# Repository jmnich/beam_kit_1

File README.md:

# Beam Kit 1

Open Source educational eval kit built around Raspberry Pi Pico. Designed for Raspberry Pi Pico 2W.

## 🚀 Features
- Socket for RPI Pico module
- Integrated debug probe with separate USB C socket, allowing for powering, programming and debugging the kit with a single cable
- I2C sensors, EEPROM and laser range finder
- Micro SD slot
- 4x4 WS2812 LED matrix
- industrial RS485 interface
- basic audio: analog microphone and stereo minijack output
- HAT socket
- SSD1306 OLED display
- NRF24 socket
- LEDs, knob and buttons

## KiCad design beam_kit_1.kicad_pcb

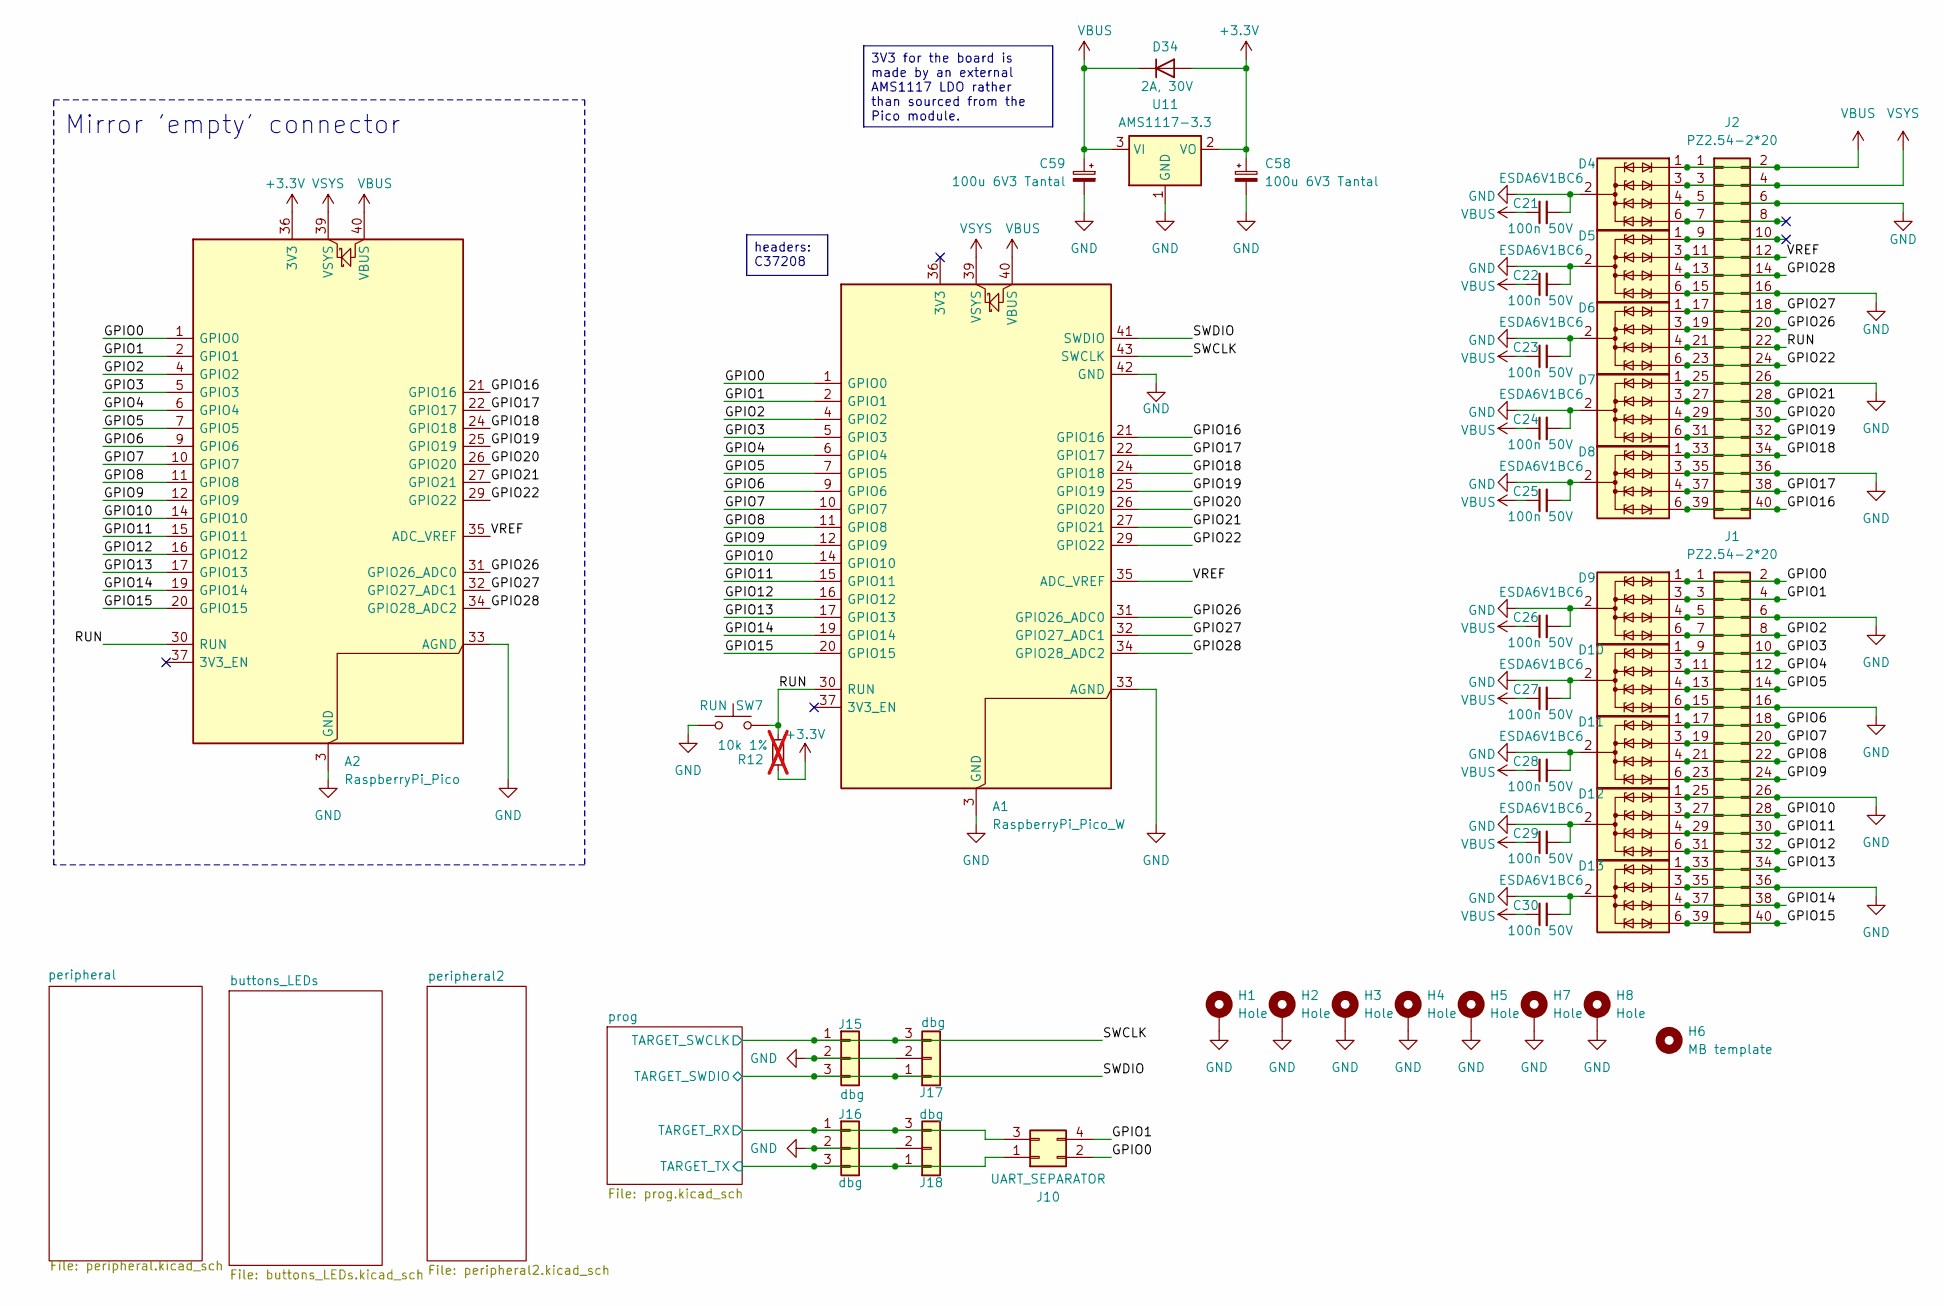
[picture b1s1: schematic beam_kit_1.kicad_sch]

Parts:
A1: RaspberryPi_Pico_W; RaspberryPi_Pico_Common
A2: RaspberryPi_Pico; RaspberryPi_Pico_Common
C21, C22, C23, C24, C25, C26, C27, C28, C29, C30: 100n 50V; C_0603_1608Metric_Pad1.08x0.95mm_HandSolder; jlc C14663
C58, C59: 100u 6V3 Tantal; CP_EIA-3528-21_Kemet-B_Pad1.50x2.35mm_HandSolder; jlc C16133
D4, D5, D6, D7, D8, D9, D10, D11, D12, D13: ESDA6V1BC6; SOT-23-6; MPN ESDA6V1BC6; jlc C495220
D34: 2A, 30V; D_PowerDI-123; MPN DFLS230LH-7; jlc C2960361
H1, H2, H3, H4, H5, H7, H8: Hole; MountingHole_3.2mm_M3_Pad_Via
H6: MB template; MountingHole_2.1mm
J1, J2: PZ2.54-2*20; PinHeader_2x20_P2.54mm_Vertical; jlc C5224014
J10: UART_SEPARATOR; PinHeader_2x02_P2.54mm_Vertical; jlc C7501273
J15, J16, J17, J18: dbg; JST_SH_BM03B-SRSS-TB_1x03-1MP_P1.00mm_Vertical; jlc C495538
R12: 10k 1%; R_0603_1608Metric_Pad0.98x0.95mm_HandSolder; jlc C25804; not fitted
SW7: RUN; SW_Push_1P1T_NO_6x6mm_H9.5mm; jlc C455112
U11: AMS1117-3.3; SOT-223-3_TabPin2; jlc C6186

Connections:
+3.3V: A2.36 (3V3), C58.1, D34.2 (A), R12.2, U11.2 (VO); also elsewhere on the board
/GPIO0: A1.1 (GPIO0), A2.1 (GPIO0), D9.1 (TVS1), J1.1, J1.2, J10.2
/GPIO1: A1.2 (GPIO1), A2.2 (GPIO1), D9.3 (TVS2), J1.3, J1.4, J10.4
/GPIO2: A1.4 (GPIO2), A2.4 (GPIO2), D9.6 (TVS4), J1.7, J1.8
/GPIO3: A1.5 (GPIO3), A2.5 (GPIO3), D10.1 (TVS1), J1.9, J1.10
/GPIO4: A1.6 (GPIO4), A2.6 (GPIO4), D10.3 (TVS2), J1.11, J1.12
/GPIO5: A1.7 (GPIO5), A2.7 (GPIO5), D10.4 (TVS3), J1.13, J1.14
/GPIO6: A1.9 (GPIO6), A2.9 (GPIO6), D11.1 (TVS1), J1.17, J1.18
/GPIO7: A1.10 (GPIO7), A2.10 (GPIO7), D11.3 (TVS2), J1.19, J1.20
/GPIO8: A1.11 (GPIO8), A2.11 (GPIO8), D11.4 (TVS3), J1.21, J1.22
/GPIO9: A1.12 (GPIO9), A2.12 (GPIO9), D11.6 (TVS4), J1.23, J1.24
/GPIO10: A1.14 (GPIO10), A2.14 (GPIO10), D12.3 (TVS2), J1.27, J1.28
/GPIO11: A1.15 (GPIO11), A2.15 (GPIO11), D12.4 (TVS3), J1.29, J1.30
/GPIO12: A1.16 (GPIO12), A2.16 (GPIO12), D12.6 (TVS4), J1.31, J1.32
/GPIO13: A1.17 (GPIO13), A2.17 (GPIO13), D13.1 (TVS1), J1.33, J1.34
/GPIO14: A1.19 (GPIO14), A2.19 (GPIO14), D13.4 (TVS3), J1.37, J1.38
/GPIO15: A1.20 (GPIO15), A2.20 (GPIO15), D13.6 (TVS4), J1.39, J1.40
/GPIO16: A1.21 (GPIO16), A2.21 (GPIO16), D8.6 (TVS4), J2.39, J2.40
/GPIO17: A1.22 (GPIO17), A2.22 (GPIO17), D8.4 (TVS3), J2.37, J2.38
/GPIO18: A1.24 (GPIO18), A2.24 (GPIO18), D8.1 (TVS1), J2.33, J2.34
/GPIO19: A1.25 (GPIO19), A2.25 (GPIO19), D7.6 (TVS4), J2.31, J2.32
/GPIO20: A1.26 (GPIO20), A2.26 (GPIO20), D7.4 (TVS3), J2.29, J2.30
/GPIO21: A1.27 (GPIO21), A2.27 (GPIO21), D7.3 (TVS2), J2.27, J2.28
/GPIO22: A1.29 (GPIO22), A2.29 (GPIO22), D6.6 (TVS4), J2.23, J2.24
/GPIO26: A1.31 (GPIO26_ADC0), A2.31 (GPIO26_ADC0), D6.3 (TVS2), J2.19, J2.20
/GPIO27: A1.32 (GPIO27_ADC1), A2.32 (GPIO27_ADC1), D6.1 (TVS1), J2.17, J2.18
/GPIO28: A1.34 (GPIO28_ADC2), A2.34 (GPIO28_ADC2), D5.4 (TVS3), J2.13, J2.14
/RUN: A1.30 (RUN), A2.30 (RUN), D6.4 (TVS3), J2.21, J2.22, R12.1, SW7.2
/SWCLK: A1.43 (SWCLK), J15.1, J17.3; also elsewhere on the board
/SWDIO: A1.41 (SWDIO), J15.3, J17.1; also elsewhere on the board
/VREF: A1.35 (ADC_VREF), A2.35 (ADC_VREF), D5.3 (TVS2), J2.11, J2.12
/prog/TARGET_RX: J10.3, J16.1, J18.3; also elsewhere on the board
/prog/TARGET_TX: J10.1, J16.3, J18.1; also elsewhere on the board
GND: A1.3 (GND), A1.8 (GND), A1.13 (GND), A1.18 (GND), A1.23 (GND), A1.28 (GND), A1.33 (AGND), A1.38 (GND), A1.42 (GND), A2.3 (GND), A2.8 (GND), A2.13 (GND), A2.18 (GND), A2.23 (GND), A2.28 (GND), A2.33 (AGND), A2.38 (GND), C21.2, C22.2, C23.2, C24.2, C25.2, C26.2, C27.2, C28.2, C29.2, C30.2, C58.2, C59.2, D4.2 (COM), D4.4 (TVS3), D4.5 (COM), D5.2 (COM), D5.5 (COM), D5.6 (TVS4), D6.2 (COM), D6.5 (COM), D7.1 (TVS1), D7.2 (COM), D7.5 (COM), D8.2 (COM), D8.3 (TVS2), D8.5 (COM), D9.2 (COM), D9.4 (TVS3), D9.5 (COM), D10.2 (COM), D10.5 (COM), D10.6 (TVS4), D11.2 (COM), D11.5 (COM), D12.1 (TVS1), D12.2 (COM), D12.5 (COM), D13.2 (COM), D13.3 (TVS2), D13.5 (COM), H1.1 (1_1), H2.1 (1_1), H3.1 (1_1), H4.1 (1_1), H5.1 (1_1), H7.1 (1_1), H8.1 (1_1), J1.5, J1.6, J1.15, J1.16, J1.25, J1.26, J1.35, J1.36, J2.5, J2.6, J2.15, J2.16, J2.25, J2.26, J2.35, J2.36, J15.2, J16.2, J17.2, J18.2, SW7.1, U11.1 (GND); also elsewhere on the board
VBUS: A1.40 (VBUS), A2.40 (VBUS), C21.1, C22.1, C23.1, C24.1, C25.1, C26.1, C27.1, C28.1, C29.1, C30.1, C59.1, D4.1 (TVS1), D34.1 (K), J2.1, J2.2, U11.3 (VI); also elsewhere on the board
VSYS: A1.39 (VSYS), A2.39 (VSYS), D4.3 (TVS2), J2.3, J2.4

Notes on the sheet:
Mirror 'empty' connector
3V3 for the board is made by an external AMS1117 LDO rather than sourced from the Pico module.
headers: C37208

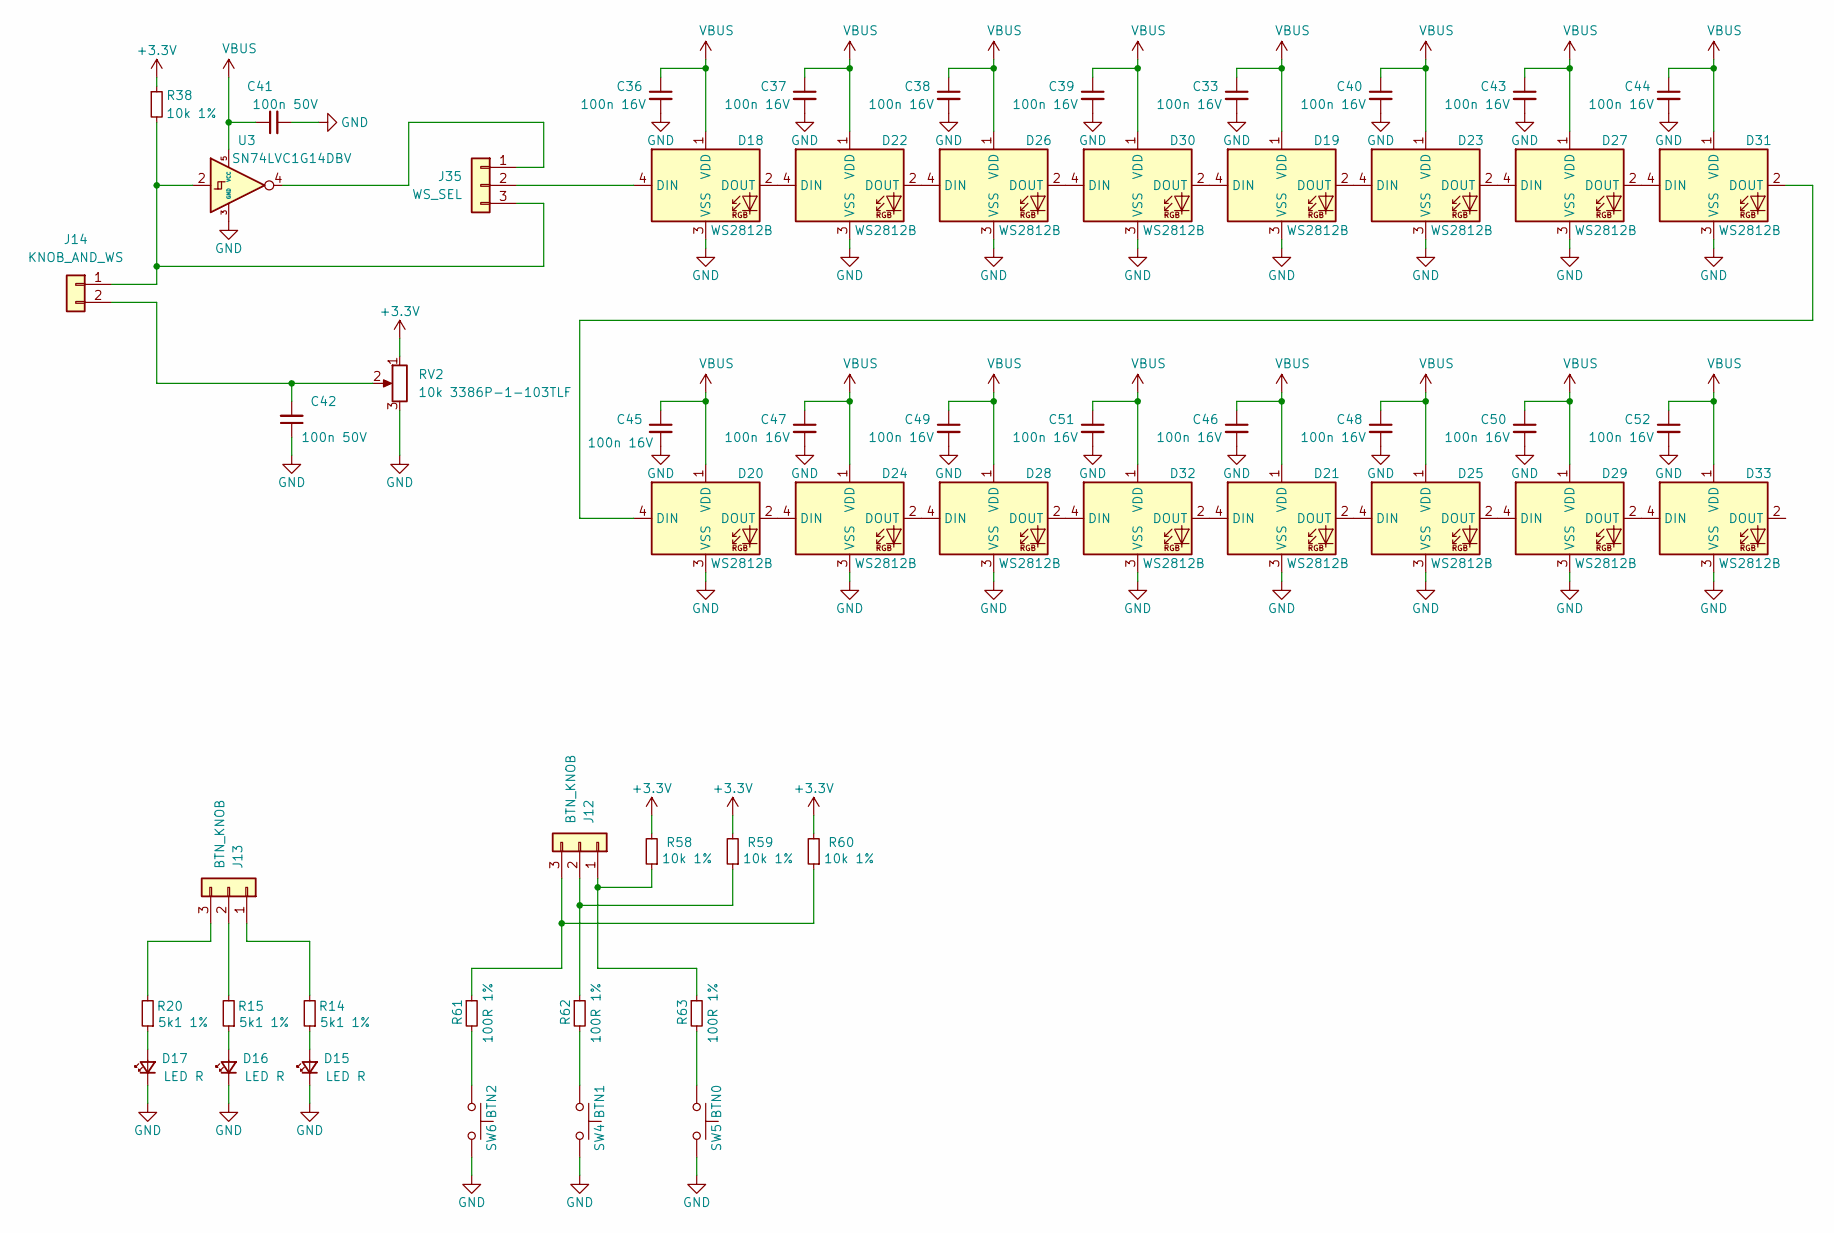
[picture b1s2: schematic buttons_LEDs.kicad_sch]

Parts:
C33, C36, C37, C38, C39, C40, C43, C44, C45, C46, C47, C48, C49, C50, C51, C52: 100n 16V; C_0402_1005Metric; MPN CL05B104KB54PNC; jlc C1525
C41, C42: 100n 50V; C_0603_1608Metric_Pad1.08x0.95mm_HandSolder; jlc C14663
D15, D16, D17: LED R; LED_0603_1608Metric_Pad1.05x0.95mm_HandSolder; jlc C2286
D18, D19, D20, D21, D22, D23, D24, D25, D26, D27, D28, D29, D30, D31, D32, D33: WS2812B; LED_WS2812B_PLCC4_5.0x5.0mm_P3.2mm; MPN XL-5050RGBC-WS2812B; jlc C2843785
J12, J13: BTN_KNOB; PinHeader_1x03_P2.54mm_Vertical; jlc C49257
J14: KNOB_AND_WS; PinHeader_1x02_P2.54mm_Vertical; jlc C492401
J35: WS_SEL; PinHeader_1x03_P2.54mm_Vertical; jlc C49257
R14, R15, R20: 5k1 1%; R_0603_1608Metric_Pad0.98x0.95mm_HandSolder; jlc C23186
R38, R58, R59, R60: 10k 1%; R_0603_1608Metric_Pad0.98x0.95mm_HandSolder; jlc C25804
R61, R62, R63: 100R 1%; R_0603_1608Metric_Pad0.98x0.95mm_HandSolder; jlc C22775
RV2: 10k 3386P-1-103TLF; Potentiometer_Bourns_3386P_Vertical; jlc C116302
SW4: BTN1; SW_Push_1P1T_NO_6x6mm_H9.5mm; jlc C455112
SW5: BTN0; SW_Push_1P1T_NO_6x6mm_H9.5mm; jlc C455112
SW6: BTN2; SW_Push_1P1T_NO_6x6mm_H9.5mm; jlc C455112
U3: SN74LVC1G14DBV; SOT-23-5; MPN SN74LVC1G14DBV; jlc C7835

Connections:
+3.3V: R38.1, R58.2, R59.2, R60.2, RV2.1; also elsewhere on the board
GND: C33.2, C36.2, C37.2, C38.2, C39.2, C40.2, C41.2, C42.1, C43.2, C44.2, C45.2, C46.2, C47.2, C48.2, C49.2, C50.2, C51.2, C52.2, D15.1 (K), D16.1 (K), D17.1 (K), D18.3 (VSS), D19.3 (VSS), D20.3 (VSS), D21.3 (VSS), D22.3 (VSS), D23.3 (VSS), D24.3 (VSS), D25.3 (VSS), D26.3 (VSS), D27.3 (VSS), D28.3 (VSS), D29.3 (VSS), D30.3 (VSS), D31.3 (VSS), D32.3 (VSS), D33.3 (VSS), RV2.3, SW4.2, SW5.2, SW6.2, U3.3 (GND); also elsewhere on the board
unnamed: D15.2 (A), R14.1
unnamed: D16.2 (A), R15.1
unnamed: D17.2 (A), R20.1
unnamed: D18.4 (DIN), J35.2
unnamed: D18.2 (DOUT), D22.4 (DIN)
unnamed: D19.4 (DIN), D30.2 (DOUT)
unnamed: D19.2 (DOUT), D23.4 (DIN)
unnamed: D20.4 (DIN), D31.2 (DOUT)
unnamed: D20.2 (DOUT), D24.4 (DIN)
unnamed: D21.4 (DIN), D32.2 (DOUT)
unnamed: D21.2 (DOUT), D25.4 (DIN)
unnamed: D22.2 (DOUT), D26.4 (DIN)
unnamed: D23.2 (DOUT), D27.4 (DIN)
unnamed: D24.2 (DOUT), D28.4 (DIN)
unnamed: D25.2 (DOUT), D29.4 (DIN)
unnamed: D26.2 (DOUT), D30.4 (DIN)
unnamed: D27.2 (DOUT), D31.4 (DIN)
unnamed: D28.2 (DOUT), D32.4 (DIN)
unnamed: D29.2 (DOUT), D33.4 (DIN)
unnamed: J12.1, R58.1, R63.1
unnamed: J12.2, R59.1, R62.1
unnamed: J12.3, R60.1, R61.1
unnamed: J13.1, R14.2
unnamed: J13.2, R15.2
unnamed: J13.3, R20.2
unnamed: J14.1, J35.3, R38.2, U3.2
unnamed: C42.2, J14.2, RV2.2
unnamed: J35.1, U3.4
unnamed: R61.2, SW6.1
unnamed: R62.2, SW4.1
unnamed: R63.2, SW5.1
VBUS: C33.1, C36.1, C37.1, C38.1, C39.1, C40.1, C41.1, C43.1, C44.1, C45.1, C46.1, C47.1, C48.1, C49.1, C50.1, C51.1, C52.1, D18.1 (VDD), D19.1 (VDD), D20.1 (VDD), D21.1 (VDD), D22.1 (VDD), D23.1 (VDD), D24.1 (VDD), D25.1 (VDD), D26.1 (VDD), D27.1 (VDD), D28.1 (VDD), D29.1 (VDD), D30.1 (VDD), D31.1 (VDD), D32.1 (VDD), D33.1 (VDD), U3.5 (VCC); also elsewhere on the board

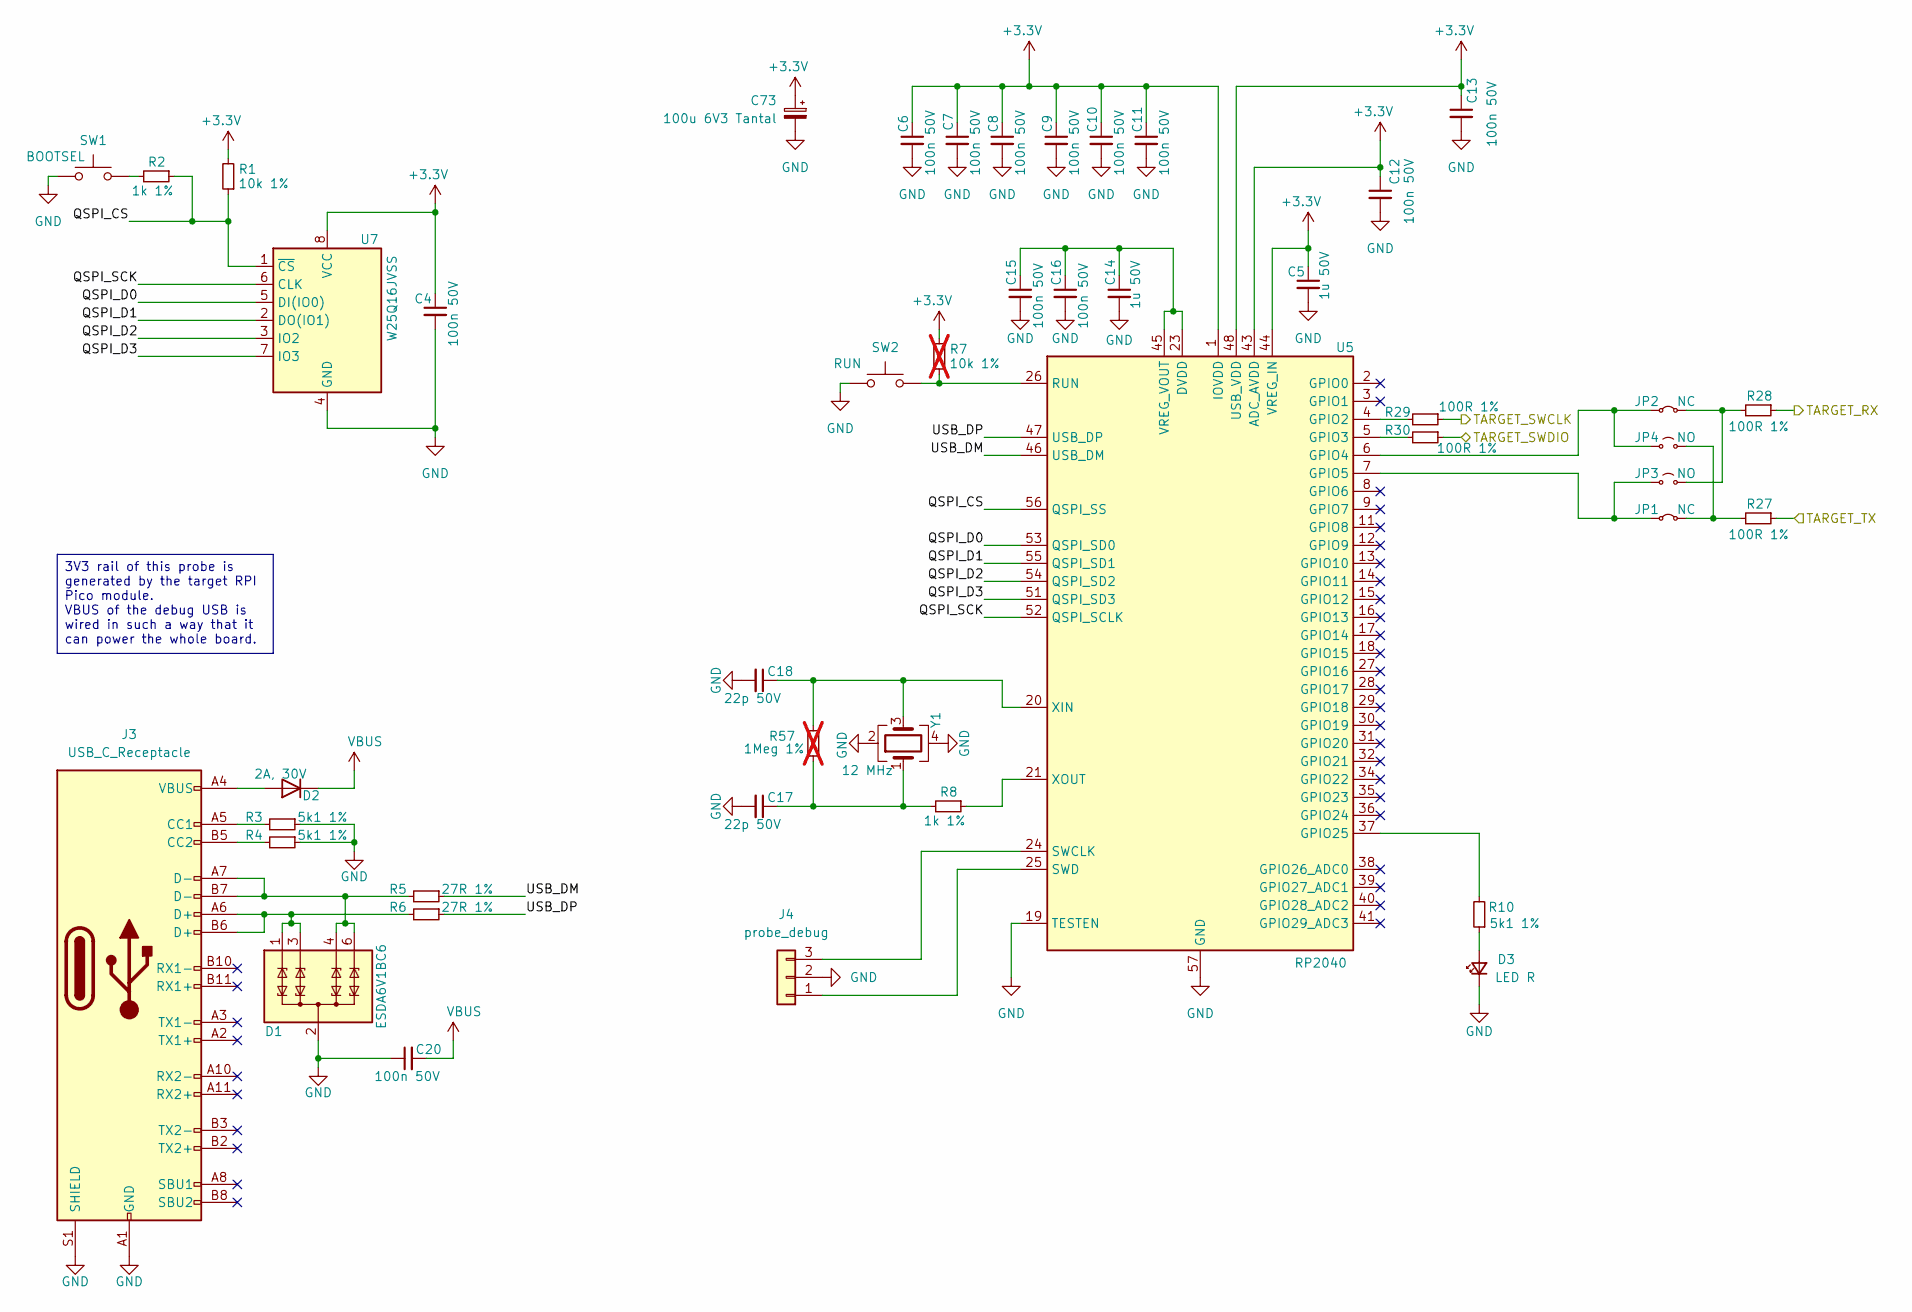
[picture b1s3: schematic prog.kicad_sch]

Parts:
C4, C6, C7, C8, C9, C10, C11, C12, C13, C15, C16, C20: 100n 50V; C_0603_1608Metric_Pad1.08x0.95mm_HandSolder; jlc C14663
C5, C14: 1u 50V; C_0603_1608Metric_Pad1.08x0.95mm_HandSolder; jlc C15849
C17, C18: 22p 50V; C_0603_1608Metric_Pad1.08x0.95mm_HandSolder; jlc C1653
C73: 100u 6V3 Tantal; CP_EIA-3528-21_Kemet-B_Pad1.50x2.35mm_HandSolder; jlc C16133
D1: ESDA6V1BC6; SOT-23-6; MPN ESDA6V1BC6; jlc C495220
D2: 2A, 30V; D_PowerDI-123; MPN DFLS230LH-7; jlc C2960361
D3: LED R; LED_0603_1608Metric_Pad1.05x0.95mm_HandSolder; jlc C2286
J3: USB_C_Receptacle; USB_C_Receptacle_Molex_105450-0101; jlc C134092
J4: probe_debug; PinHeader_1x03_P2.54mm_Vertical; jlc C49257
JP1, JP2: NC; SolderJumper-2_P1.3mm_Bridged_RoundedPad1.0x1.5mm
JP3, JP4: NO; SolderJumper-2_P1.3mm_Open_RoundedPad1.0x1.5mm
R1: 10k 1%; R_0603_1608Metric_Pad0.98x0.95mm_HandSolder; jlc C25804
R2, R8: 1k 1%; R_0603_1608Metric_Pad0.98x0.95mm_HandSolder; jlc C21190
R3, R4, R10: 5k1 1%; R_0603_1608Metric_Pad0.98x0.95mm_HandSolder; jlc C23186
R5, R6: 27R 1%; R_0603_1608Metric_Pad0.98x0.95mm_HandSolder; jlc C25190
R7: 10k 1%; R_0603_1608Metric_Pad0.98x0.95mm_HandSolder; jlc C25804; not fitted
R27, R28, R29, R30: 100R 1%; R_0603_1608Metric_Pad0.98x0.95mm_HandSolder; jlc C22775
R57: 1Meg 1%; R_0603_1608Metric_Pad0.98x0.95mm_HandSolder; not fitted
SW1: BOOTSEL; SW_SPST_B3U-1000P; jlc C231329
SW2: RUN; SW_SPST_B3U-1000P; jlc C231329
U5: RP2040; QFN-56-1EP_7x7mm_P0.4mm_EP3.2x3.2mm; jlc C2040
U7: W25Q16JVSS; SOIC-8_5.23x5.23mm_P1.27mm; jlc C131025
Y1: 12 MHz; Crystal_SMD_3225-4Pin_3.2x2.5mm; MPN X322512MSB4SI; jlc C9002

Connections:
+3.3V: C4.1, C5.1, C6.1, C7.1, C8.1, C9.1, C10.1, C11.1, C12.1, C13.1, C73.1, R1.2, R7.2, U5.1 (IOVDD), U5.10 (IOVDD), U5.22 (IOVDD), U5.33 (IOVDD), U5.42 (IOVDD), U5.43 (ADC_AVDD), U5.44 (VREG_IN), U5.48 (USB_VDD), U5.49 (IOVDD), U7.8 (VCC); also elsewhere on the board
/SWCLK: R29.1; also elsewhere on the board
/SWDIO: R30.1; also elsewhere on the board
/prog/QSPI_CS: R1.1, R2.1, U5.56 (QSPI_SS), U7.1 (~CS)
/prog/QSPI_D0: U5.53 (QSPI_SD0), U7.5 (DI(IO0))
/prog/QSPI_D1: U5.55 (QSPI_SD1), U7.2 (DO(IO1))
/prog/QSPI_D2: U5.54 (QSPI_SD2), U7.3 (IO2)
/prog/QSPI_D3: U5.51 (QSPI_SD3), U7.7 (IO3)
/prog/QSPI_SCK: U5.52 (QSPI_SCLK), U7.6 (CLK)
/prog/TARGET_RX: R28.1; also elsewhere on the board
/prog/TARGET_TX: R27.1; also elsewhere on the board
/prog/USB_DM: R5.1, U5.46 (USB_DM)
/prog/USB_DP: R6.1, U5.47 (USB_DP)
GND: C4.2, C5.2, C6.2, C7.2, C8.2, C9.2, C10.2, C11.2, C12.2, C13.2, C14.2, C15.2, C16.2, C17.2, C18.2, C20.1, C73.2, D1.2 (COM), D1.5 (COM), D3.1 (K), J3.A1 (GND), J3.A12 (GND), J3.B1 (GND), J3.B12 (GND), J3.S1 (SHIELD), J4.2, R3.1, R4.1, SW1.1, SW2.1, U5.19 (TESTEN), U5.57 (GND), U7.4 (GND), Y1.2, Y1.4; also elsewhere on the board
unnamed: C17.1, R8.2, R57.2, Y1.1
unnamed: D1.1 (TVS1), D1.3 (TVS2), J3.A6 (D+), J3.B6 (D+), R6.2
unnamed: D1.4 (TVS3), D1.6 (TVS4), J3.A7 (D-), J3.B7 (D-), R5.2
unnamed: D2.2 (A), J3.A4 (VBUS), J3.A9 (VBUS), J3.B4 (VBUS), J3.B9 (VBUS)
unnamed: D3.2 (A), R10.1
unnamed: J3.A5 (CC1), R3.2
unnamed: J3.B5 (CC2), R4.2
unnamed: J4.1, U5.25 (SWD)
unnamed: J4.3, U5.24 (SWCLK)
unnamed: JP1.1 (A), JP3.1 (A), U5.7 (GPIO5)
unnamed: JP1.2 (B), JP4.2 (B), R27.2
unnamed: JP2.1 (A), JP4.1 (A), U5.6 (GPIO4)
unnamed: JP2.2 (B), JP3.2 (B), R28.2
unnamed: R2.2, SW1.2
unnamed: R29.2, U5.4 (GPIO2)
unnamed: R30.2, U5.5 (GPIO3)
unnamed: R10.2, U5.37 (GPIO25)
unnamed: R7.1, SW2.2, U5.26 (RUN)
unnamed: C14.1, C15.1, C16.1, U5.23 (DVDD), U5.45 (VREG_VOUT), U5.50 (DVDD)
unnamed: C18.1, R57.1, U5.20 (XIN), Y1.3
unnamed: R8.1, U5.21 (XOUT)
VBUS: C20.2, D2.1 (K); also elsewhere on the board

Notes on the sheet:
3V3 rail of this probe is generated by the target RPI Pico module. VBUS of the debug USB is wired in such a way that it can power the whole board.

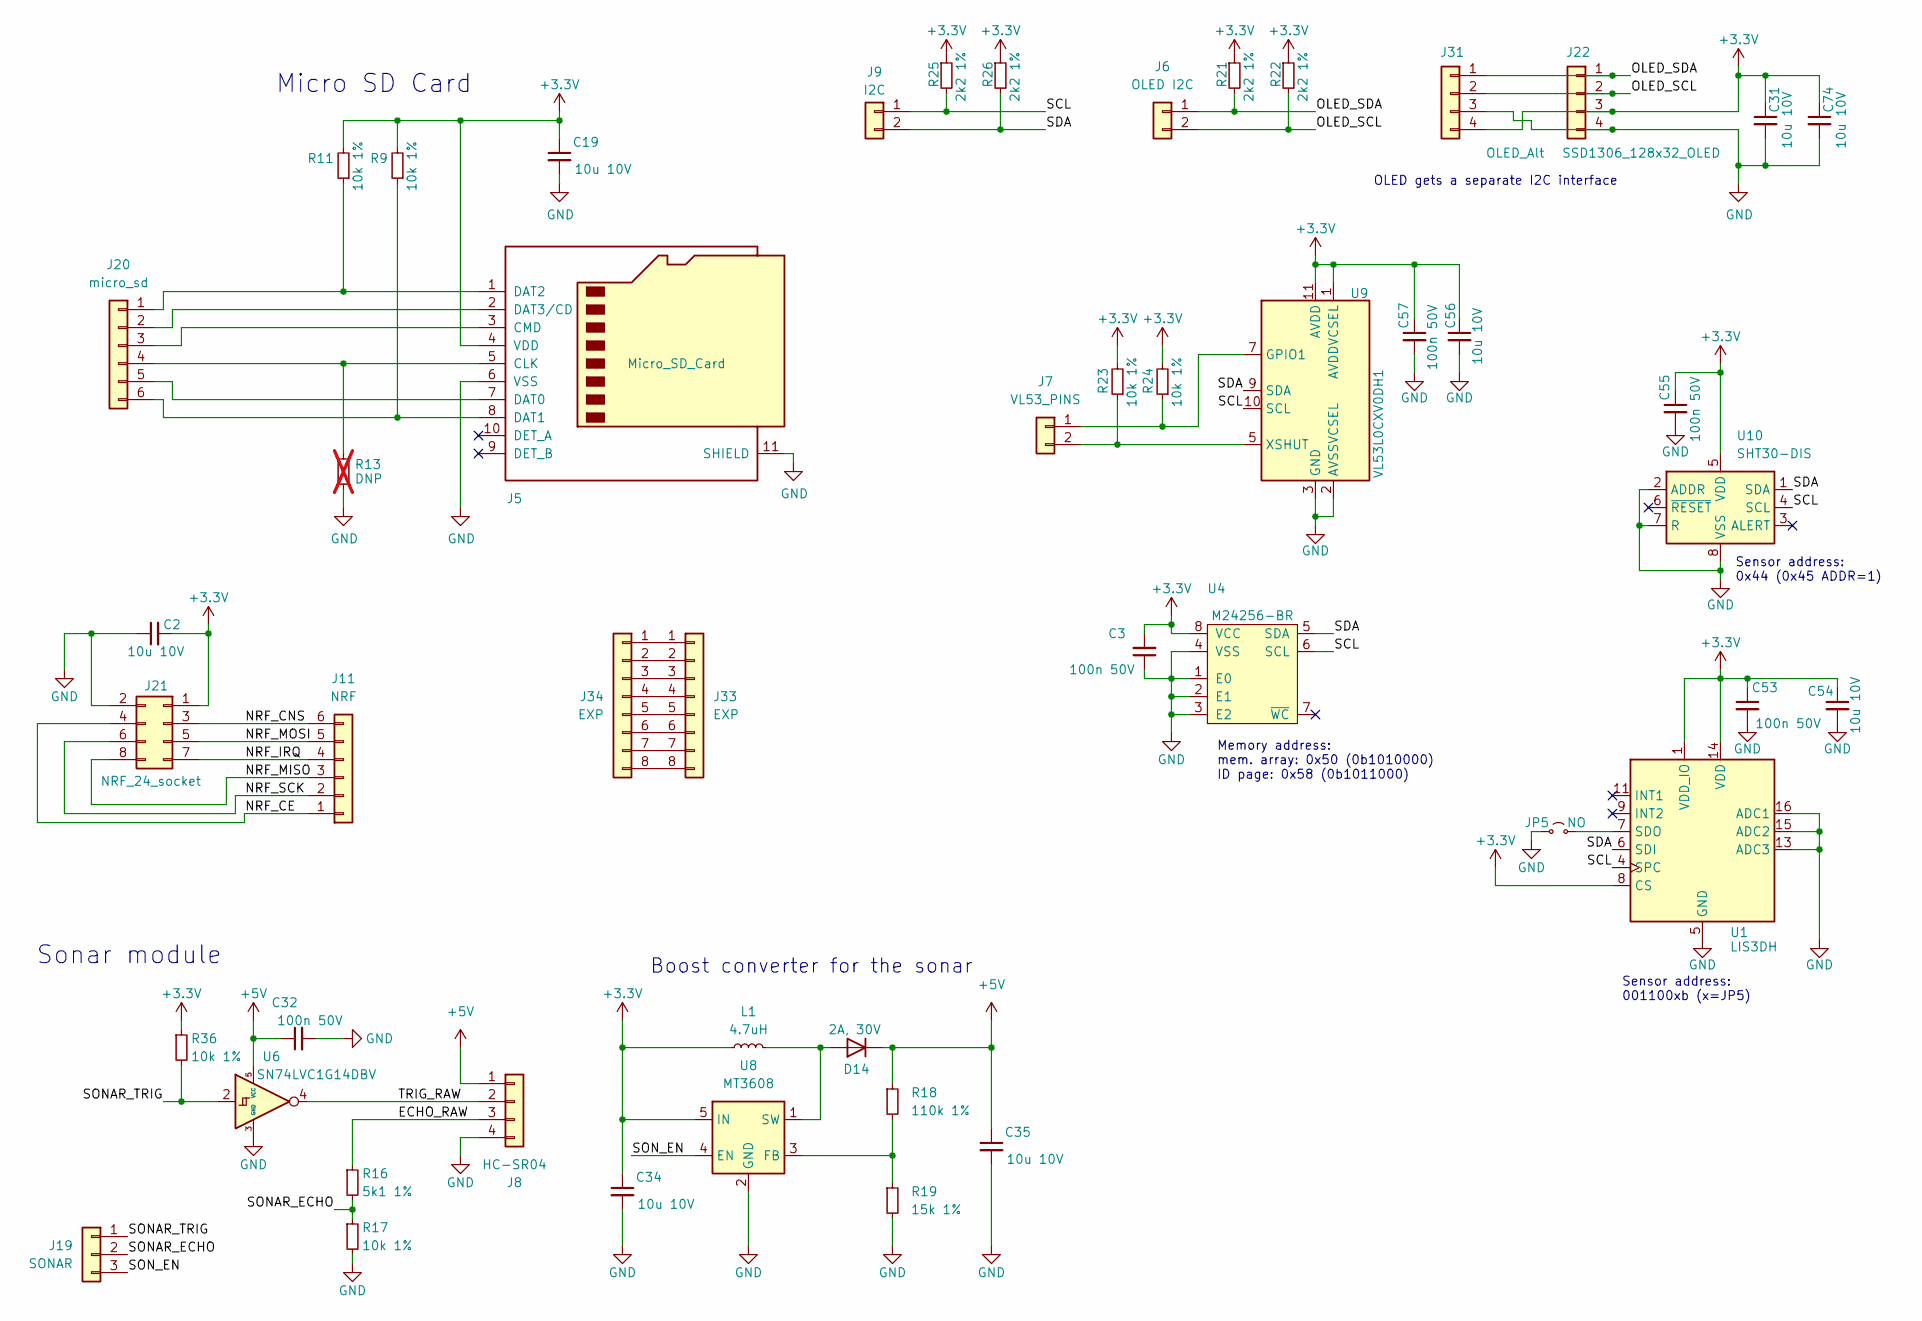
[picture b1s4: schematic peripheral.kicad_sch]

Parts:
C2, C19, C31, C34, C35, C54, C56, C74: 10u 10V; C_0603_1608Metric_Pad1.08x0.95mm_HandSolder; jlc C19702
C3, C32, C53, C55, C57: 100n 50V; C_0603_1608Metric_Pad1.08x0.95mm_HandSolder; jlc C14663
D14: 2A, 30V; D_PowerDI-123; MPN DFLS230LH-7; jlc C2960361
J5: Micro_SD_Card; microSD_HC_Molex_104031-0811; jlc C585350
J6: OLED I2C; PinHeader_1x02_P2.54mm_Vertical; jlc C492401
J7: VL53_PINS; PinHeader_1x02_P2.54mm_Vertical; jlc C492401
J8: HC-SR04; PinSocket_1x04_P2.54mm_Vertical; jlc C2718488
J9: I2C; PinHeader_1x02_P2.54mm_Vertical; jlc C492401
J11: NRF; PinHeader_1x06_P2.54mm_Vertical; jlc C37208
J19: SONAR; PinHeader_1x03_P2.54mm_Vertical; jlc C49257
J20: micro_sd; PinHeader_1x06_P2.54mm_Vertical; jlc C37208
J21: NRF_24_socket; PinSocket_2x04_P2.54mm_Vertical; jlc C92271
J22: SSD1306_128x32_OLED; PinSocket_1x04_P2.54mm_Vertical; jlc C2718488
J31: OLED_Alt; PinSocket_1x04_P2.54mm_Vertical; jlc C2718488
J33: EXP; PinHeader_1x08_P2.54mm_Vertical; jlc C18078205
J34: EXP; PinSocket_1x08_P2.54mm_Vertical; jlc C5224027
JP5: NO; SolderJumper-2_P1.3mm_Open_RoundedPad1.0x1.5mm
L1: 4.7uH; L_1206_3216Metric_Pad1.22x1.90mm_HandSolder; MPN CMP321609UD4R7MT; jlc C139250
R9, R11, R17, R23, R24, R36: 10k 1%; R_0603_1608Metric_Pad0.98x0.95mm_HandSolder; jlc C25804
R13: DNP; R_0603_1608Metric_Pad0.98x0.95mm_HandSolder; not fitted
R16: 5k1 1%; R_0603_1608Metric_Pad0.98x0.95mm_HandSolder; jlc C23186
R18: 110k 1%; R_0603_1608Metric_Pad0.98x0.95mm_HandSolder; jlc C25805
R19: 15k 1%; R_0603_1608Metric_Pad0.98x0.95mm_HandSolder; jlc C22809
R21, R22, R25, R26: 2k2 1%; R_0603_1608Metric_Pad0.98x0.95mm_HandSolder; jlc C4190
U1: LIS3DH; LGA-16_3x3mm_P0.5mm_LayoutBorder3x5y; jlc C15134
U4: M24256-BR; SOIC-8_3.9x4.9mm_P1.27mm; MPN M24256-BRMN6TP; jlc C79984
U6: SN74LVC1G14DBV; SOT-23-5; MPN SN74LVC1G14DBV; jlc C7835
U8: MT3608; SOT-23-6; jlc C84817
U9: VL53L0CXV0DH1; ST_VL53L1x; jlc C91199
U10: SHT30-DIS; Sensirion_DFN-8-1EP_2.5x2.5mm_P0.5mm_EP1.1x1.7mm; jlc C2687423

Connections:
+3.3V: C2.2, C3.2, C19.1, C31.1, C34.1, C53.1, C54.1, C55.1, C56.1, C57.1, C74.1, J5.4 (VDD), J21.1, J22.3, J31.4, L1.1, R9.2, R11.2, R21.1, R22.1, R23.2, R24.2, R25.1, R26.1, R36.1, U1.1 (VDD_IO), U1.8 (CS), U1.14 (VDD), U4.8 (VCC), U8.5 (IN), U9.1 (AVDDVCSEL), U9.11 (AVDD), U10.5 (VDD); also elsewhere on the board
+5V: C32.1, C35.1, D14.1 (K), J8.1, R18.1, U6.5 (VCC)
/peripheral/ECHO_RAW: J8.3, R16.1
/peripheral/NRF_CE: J11.1, J21.4
/peripheral/NRF_CNS: J11.6, J21.3
/peripheral/NRF_IRQ: J11.4, J21.7
/peripheral/NRF_MISO: J11.3, J21.8
/peripheral/NRF_MOSI: J11.5, J21.5
/peripheral/NRF_SCK: J11.2, J21.6
/peripheral/OLED_SCL: J6.2, J22.2, J31.2, R22.2
/peripheral/OLED_SDA: J6.1, J22.1, J31.1, R21.2
/peripheral/SCL: J9.1, R25.2, U1.4 (SPC), U4.6 (SCL), U9.10 (SCL), U10.4 (SCL)
/peripheral/SDA: J9.2, R26.2, U1.6 (SDI), U4.5 (SDA), U9.9 (SDA), U10.1 (SDA)
/peripheral/SONAR_ECHO: J19.2, R16.2, R17.1
/peripheral/SONAR_TRIG: J19.1, R36.2, U6.2
/peripheral/SON_EN: J19.3, U8.4 (EN)
/peripheral/TRIG_RAW: J8.2, U6.4
GND: C2.1, C3.1, C19.2, C31.2, C32.2, C34.2, C35.2, C53.2, C54.2, C55.2, C56.2, C57.2, C74.2, J5.6 (VSS), J5.11 (SHIELD), J8.4, J21.2, J22.4, J31.3, JP5.1 (A), R13.2, R17.2, R19.2, U1.5 (GND), U1.10 (GND), U1.12 (GND), U1.13 (ADC3), U1.15 (ADC2), U1.16 (ADC1), U4.1 (E0), U4.2 (E1), U4.3 (E2), U4.4 (VSS), U6.3 (GND), U8.2 (GND), U9.2 (AVSSVCSEL), U9.3 (GND), U9.4 (GND), U9.6 (GND), U9.12 (GND), U10.2 (ADDR), U10.7 (R), U10.8 (VSS), U10.9 (VSS); also elsewhere on the board
unnamed: D14.2 (A), L1.2, U8.1 (SW)
unnamed: J7.1, R24.1, U9.7 (GPIO1)
unnamed: J7.2, R23.1, U9.5 (XSHUT)
unnamed: J5.1 (DAT2), J20.1, R11.1
unnamed: J5.2 (DAT3/CD), J20.2
unnamed: J5.3 (CMD), J20.3
unnamed: J5.5 (CLK), J20.4, R13.1
unnamed: J5.7 (DAT0), J20.5
unnamed: J5.8 (DAT1), J20.6, R9.1
unnamed: J33.1, J34.1
unnamed: J33.2, J34.2
unnamed: J33.3, J34.3
unnamed: J33.4, J34.4
unnamed: J33.5, J34.5
unnamed: J33.6, J34.6
unnamed: J33.7, J34.7
unnamed: J33.8, J34.8
unnamed: JP5.2 (B), U1.7 (SDO)
unnamed: R18.2, R19.1, U8.3 (FB)

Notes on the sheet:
Micro SD Card
Boost converter for the sonar
Memory address: mem. array: 0x50 (0b1010000) ID page: 0x58 (0b1011000)
Sensor address: 0x44 (0x45 ADDR=1)
Sonar module
Sensor address: 001100xb (x=JP5)
OLED gets a separate I2C interface
